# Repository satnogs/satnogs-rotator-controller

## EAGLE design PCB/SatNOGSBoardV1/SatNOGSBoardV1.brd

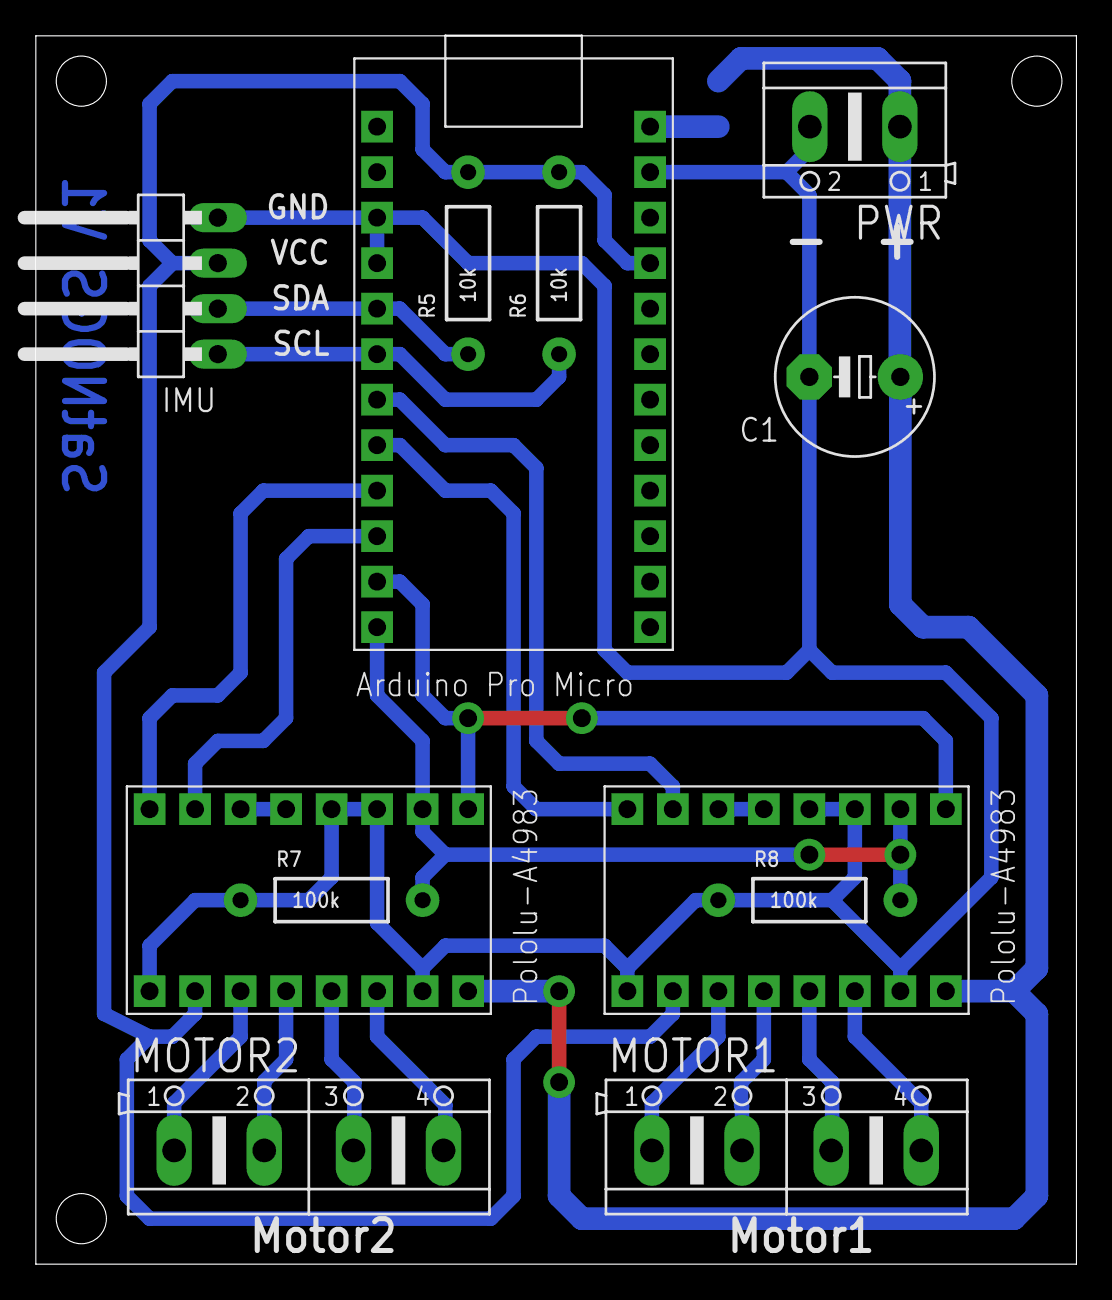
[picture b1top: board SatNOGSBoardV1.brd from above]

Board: 2 copper layers, 58.1 x 68.6 mm, 13 parts (1 on the bottom side), 22 nets.

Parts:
C1: 1000u; E5-8,5
DRIVER1, DRIVER2: POLOLU-A4983POLOLU-A4983; POLOLU-A4983
IMU: 10DOF; 1X04/90
MOTOR1: con2; AK500/4
MOTOR2: con3; AK500/4
PWR: con1; AK500/2
R5, R6: 10k; AXIAL-0.4
R7, R8: 100k; AXIAL-0.4
SJ1: SJ1; SJW
UC: ARDUINO_PRO_MICROARDUINO_BOARD; ARDUINO_MICRO_PRO

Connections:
1-1A: DRIVER1.12, MOTOR1.2
1-1B: DRIVER1.11, MOTOR1.1
1-2A: DRIVER1.13, MOTOR1.3
1-2B: DRIVER1.14, MOTOR1.4
2-1A: DRIVER2.12, MOTOR2.2
2-1B: DRIVER2.11, MOTOR2.1
2-2A: DRIVER2.13, MOTOR2.3
2-2B: DRIVER2.14, MOTOR2.4
DIR-1: DRIVER1.8, UC.8
DIR-2: DRIVER2.8, UC.9
GND: C1.-, DRIVER1.3, DRIVER1.4, DRIVER1.9, DRIVER1.15, DRIVER2.3, DRIVER2.4, DRIVER2.9, DRIVER2.15, IMU.4, PWR.2, R7.P$1, R8.P$1, UC.3, UC.4, UC.23
MS1: DRIVER1.2, DRIVER2.2, R7.P$2, R8.P$2, UC.12
M_EN: DRIVER1.1, DRIVER2.1, UC.11
unnamed: DRIVER1.5, DRIVER1.6
unnamed: DRIVER2.5, DRIVER2.6
unnamed: SJ1.1, UC.24
SCL: IMU.1, R6.P$1, UC.6
SDA: IMU.2, R5.P$1, UC.5
STEP-1: DRIVER1.7, UC.7
STEP-2: DRIVER2.7, UC.10
VCC: DRIVER1.10, DRIVER2.10, IMU.3, R5.P$2, R6.P$2, UC.21
VMOTOR: C1.+, DRIVER1.16, DRIVER2.16, PWR.1, SJ1.2

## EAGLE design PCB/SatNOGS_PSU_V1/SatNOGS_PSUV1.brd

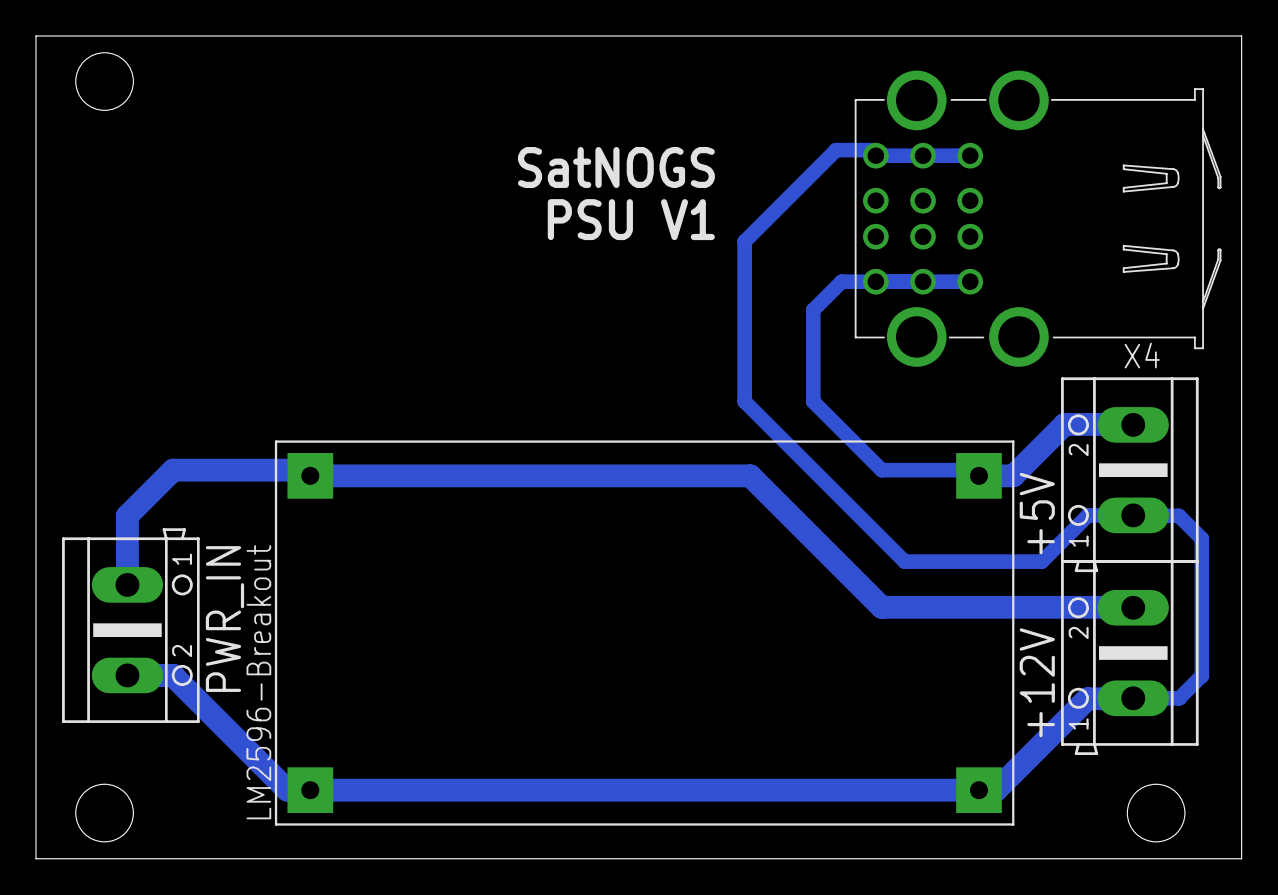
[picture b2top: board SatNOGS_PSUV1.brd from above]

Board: 2 copper layers, 67.0 x 45.7 mm, 5 parts (0 on the bottom side), 3 nets.

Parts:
+5V: 3; AK500/2
+12V: 2; AK500/2
PWR_IN: 1; AK500/2
U$1: LM2596-BREAKOUTLM2596-BREAKOUT; LM2596-BREAKOUT
X4: USB_3PSHIELD-85-32003-00X-1; 85-32003-00X-1

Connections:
+5V: +5V.2, U$1.3, X4.1-1, X4.2-1, X4.3-1
+12V: +12V.2, PWR_IN.1, U$1.4
GND: +5V.1, +12V.1, PWR_IN.2, U$1.1, U$1.2, X4.1-4, X4.2-4, X4.3-4

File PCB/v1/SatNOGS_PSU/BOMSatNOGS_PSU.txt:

Part   Value                          Device                         Package         Description                                             
+5V    3                              AK500/2                        AK500/2         CONNECTOR                                               
LM2596 LM2596-BREAKOUTLM2596-BREAKOUT LM2596-BREAKOUTLM2596-BREAKOUT LM2596-BREAKOUT Break out for LM2596 Switching power supply (regulated) 
VIN    1                              AK500/2                        AK500/2         CONNECTOR                                               
VOUT   2                              AK500/2                        AK500/2         CONNECTOR                                               
X4     USB_3PSHIELD-85-32003-00X-1    USB_3PSHIELD-85-32003-00X-1    85-32003-00X-1  Triple USB Connector

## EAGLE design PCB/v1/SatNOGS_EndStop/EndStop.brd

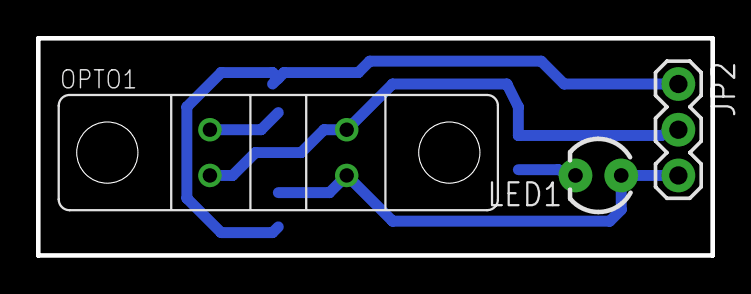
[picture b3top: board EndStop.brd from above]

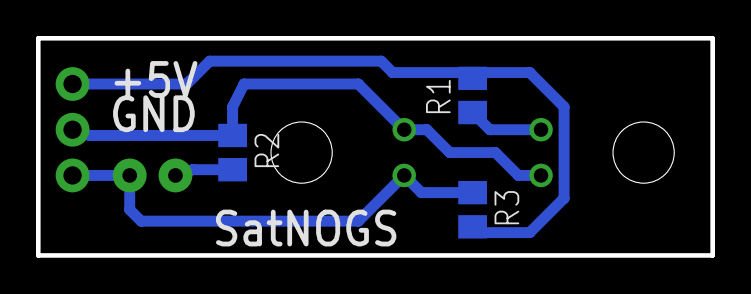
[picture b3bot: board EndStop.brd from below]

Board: 2 copper layers, 37.5 x 12.1 mm, 6 parts (3 on the bottom side), 5 nets.

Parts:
JP2: 1X03
LED1: LED3MM
OPTO1: TCST2103; TCST2013
R1: 180; M0805
R2: 150; M0805
R3: 2k2; M0805

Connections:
GND: JP2.2, OPTO1.LED_K, OPTO1.NPN_E, R2.1
unnamed: OPTO1.LED_A, R1.1
unnamed: LED1.K, R2.2
SIGNAL: JP2.3, LED1.A, OPTO1.NPN_C, R3.1
VCC: JP2.1, R1.2, R3.2

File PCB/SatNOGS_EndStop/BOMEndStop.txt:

Part  Value    Device     Package  Description               
JP2            M03PTH     1X03     Header 3                  
LED1           LED3MM     LED3MM   LEDs                      
OPTO1 TCST2103 TCST2103   TCST2013                           
R1    180      R-EU_M0805 M0805    RESISTOR, European symbol 
R2    150      R-EU_M0805 M0805    RESISTOR, European symbol 
R3    2k2      R-EU_M0805 M0805    RESISTOR, European symbol

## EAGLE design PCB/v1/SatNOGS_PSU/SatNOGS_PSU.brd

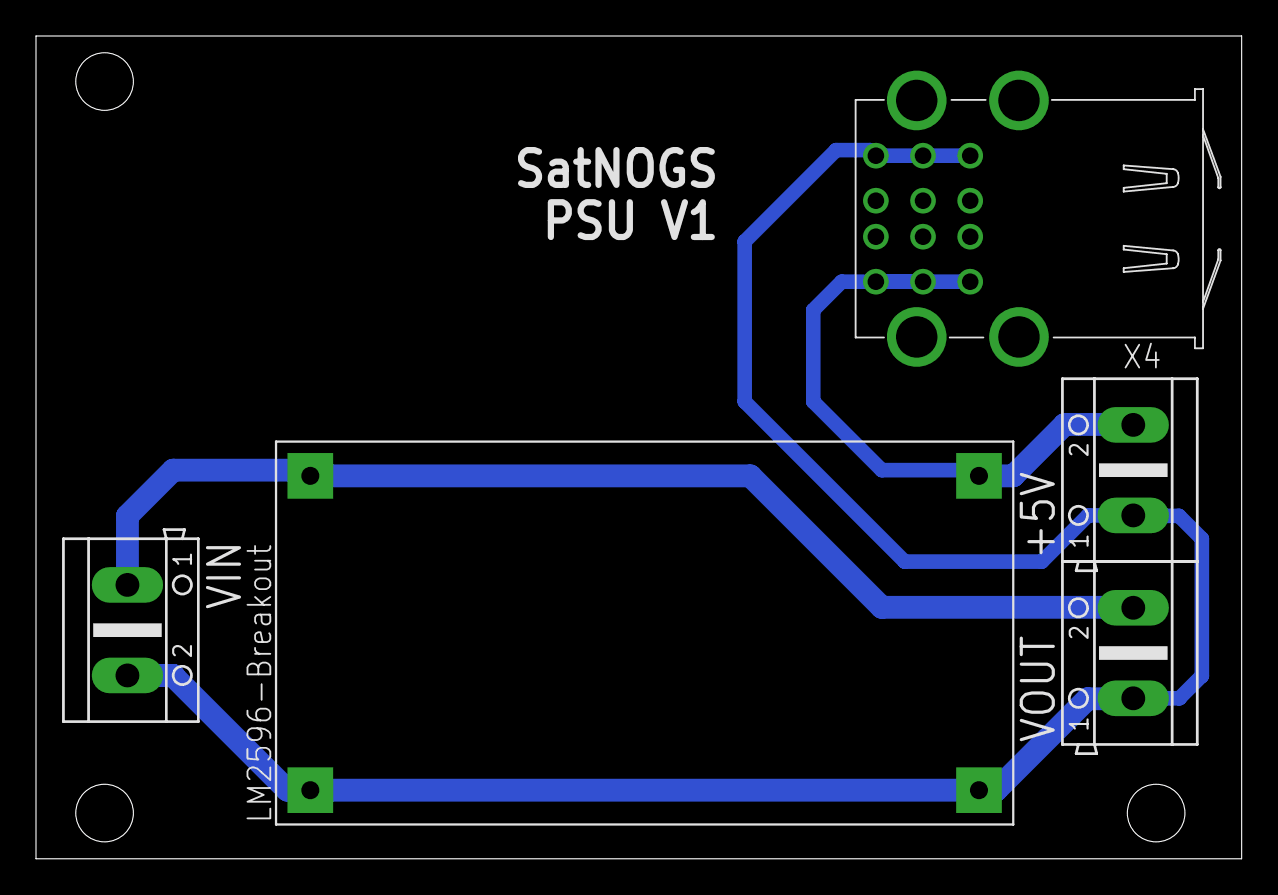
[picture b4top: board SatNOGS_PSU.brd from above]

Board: 2 copper layers, 67.0 x 45.7 mm, 5 parts (0 on the bottom side), 3 nets.

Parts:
+5V: 3; AK500/2
LM2596: LM2596-BREAKOUTLM2596-BREAKOUT; LM2596-BREAKOUT
VIN: 1; AK500/2
VOUT: 2; AK500/2
X4: USB_3PSHIELD-85-32003-00X-1; 85-32003-00X-1

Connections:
+5V: +5V.2, LM2596.3, X4.1-1, X4.2-1, X4.3-1
GND: +5V.1, LM2596.1, LM2596.2, VIN.2, VOUT.1, X4.1-4, X4.2-4, X4.3-4
VIN: LM2596.4, VIN.1, VOUT.2

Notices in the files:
parts and their libraries:
SparkFun-Resistors: Licensing: CC v3.0 Share-Alike You are welcome to use this library for commercial purposes.
SparkFun-LED: Licensing: Creative Commons ShareAlike 4.0 International - https://creativecommons.org/licenses/by-sa/4.0
